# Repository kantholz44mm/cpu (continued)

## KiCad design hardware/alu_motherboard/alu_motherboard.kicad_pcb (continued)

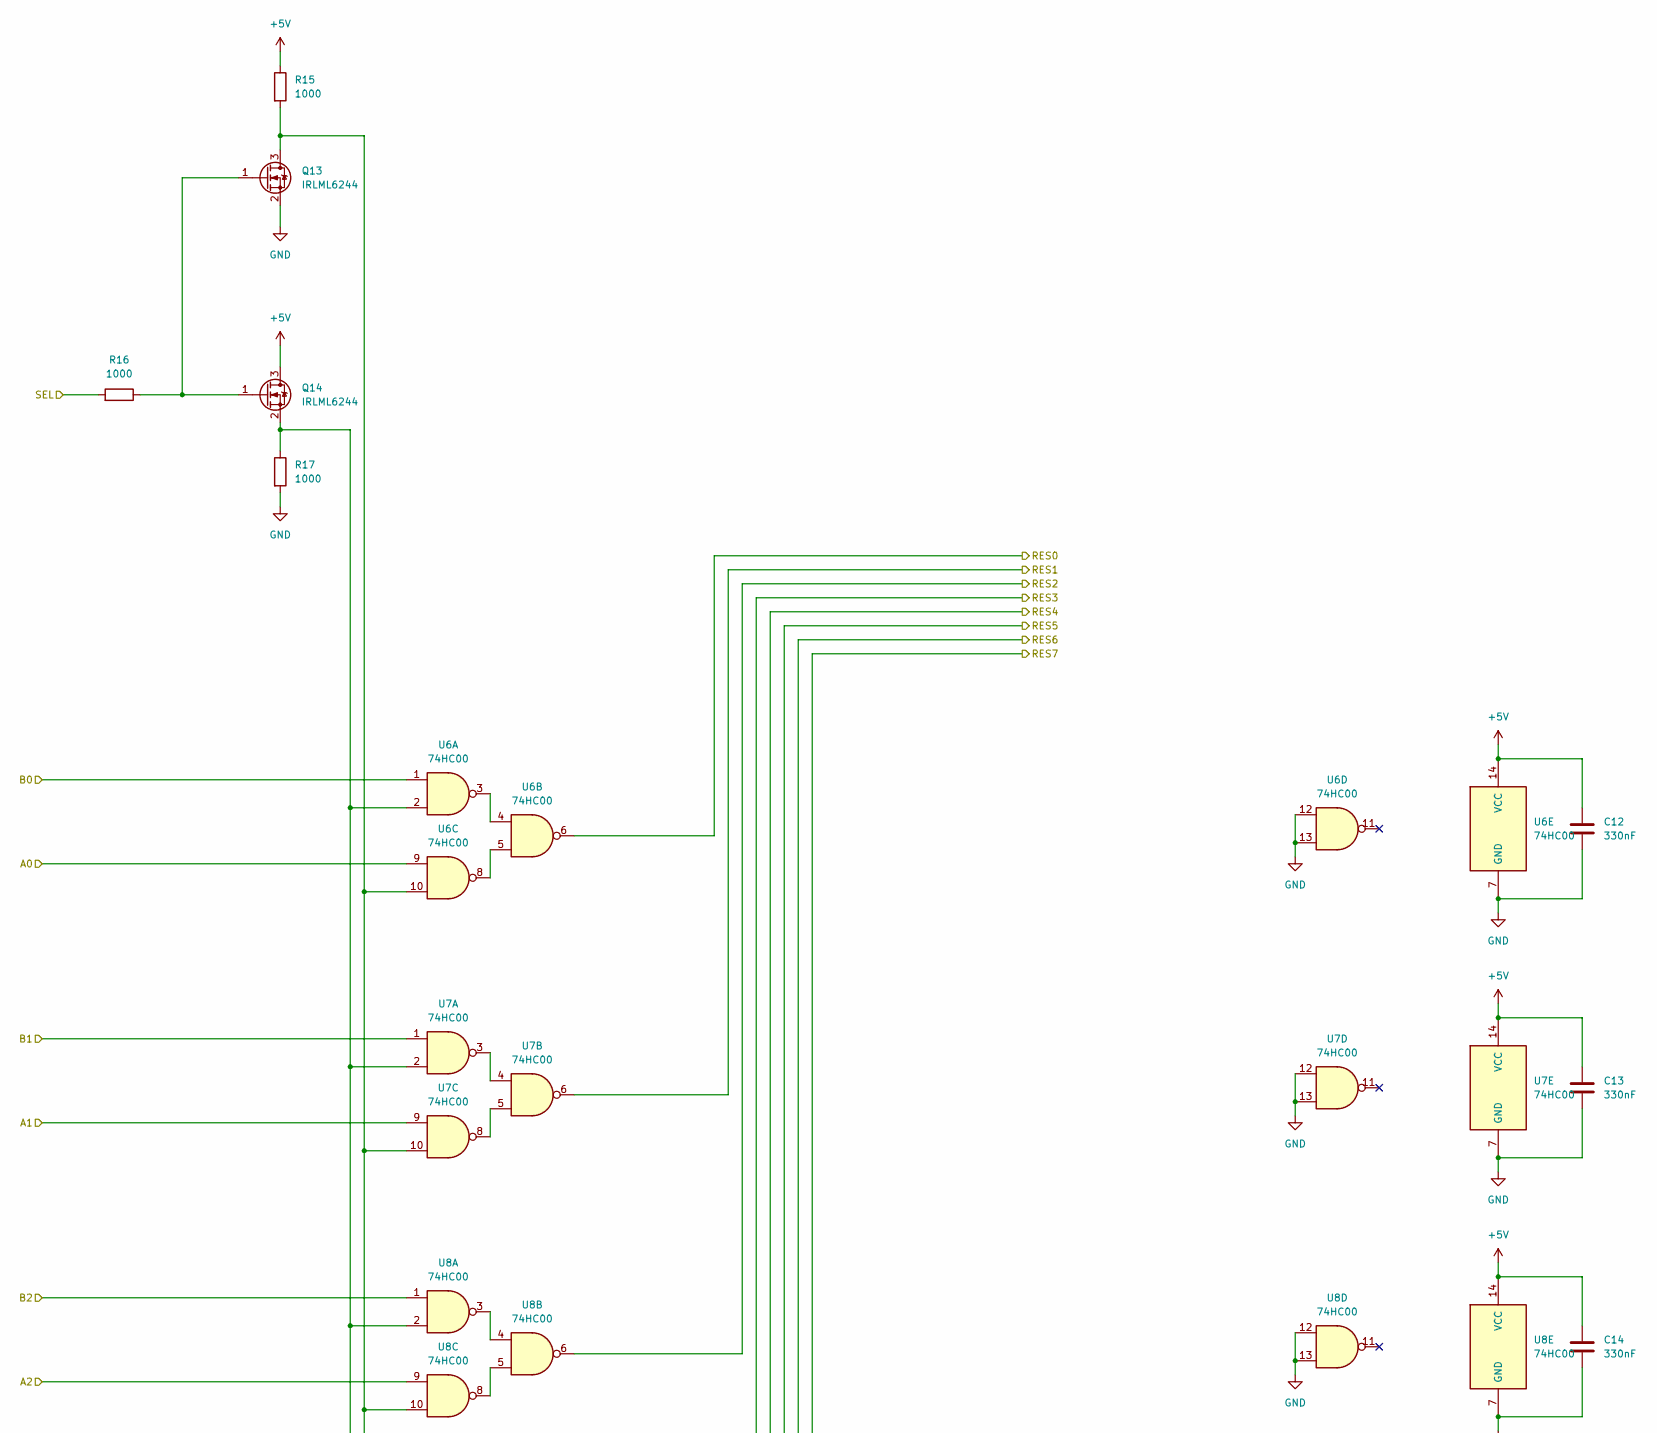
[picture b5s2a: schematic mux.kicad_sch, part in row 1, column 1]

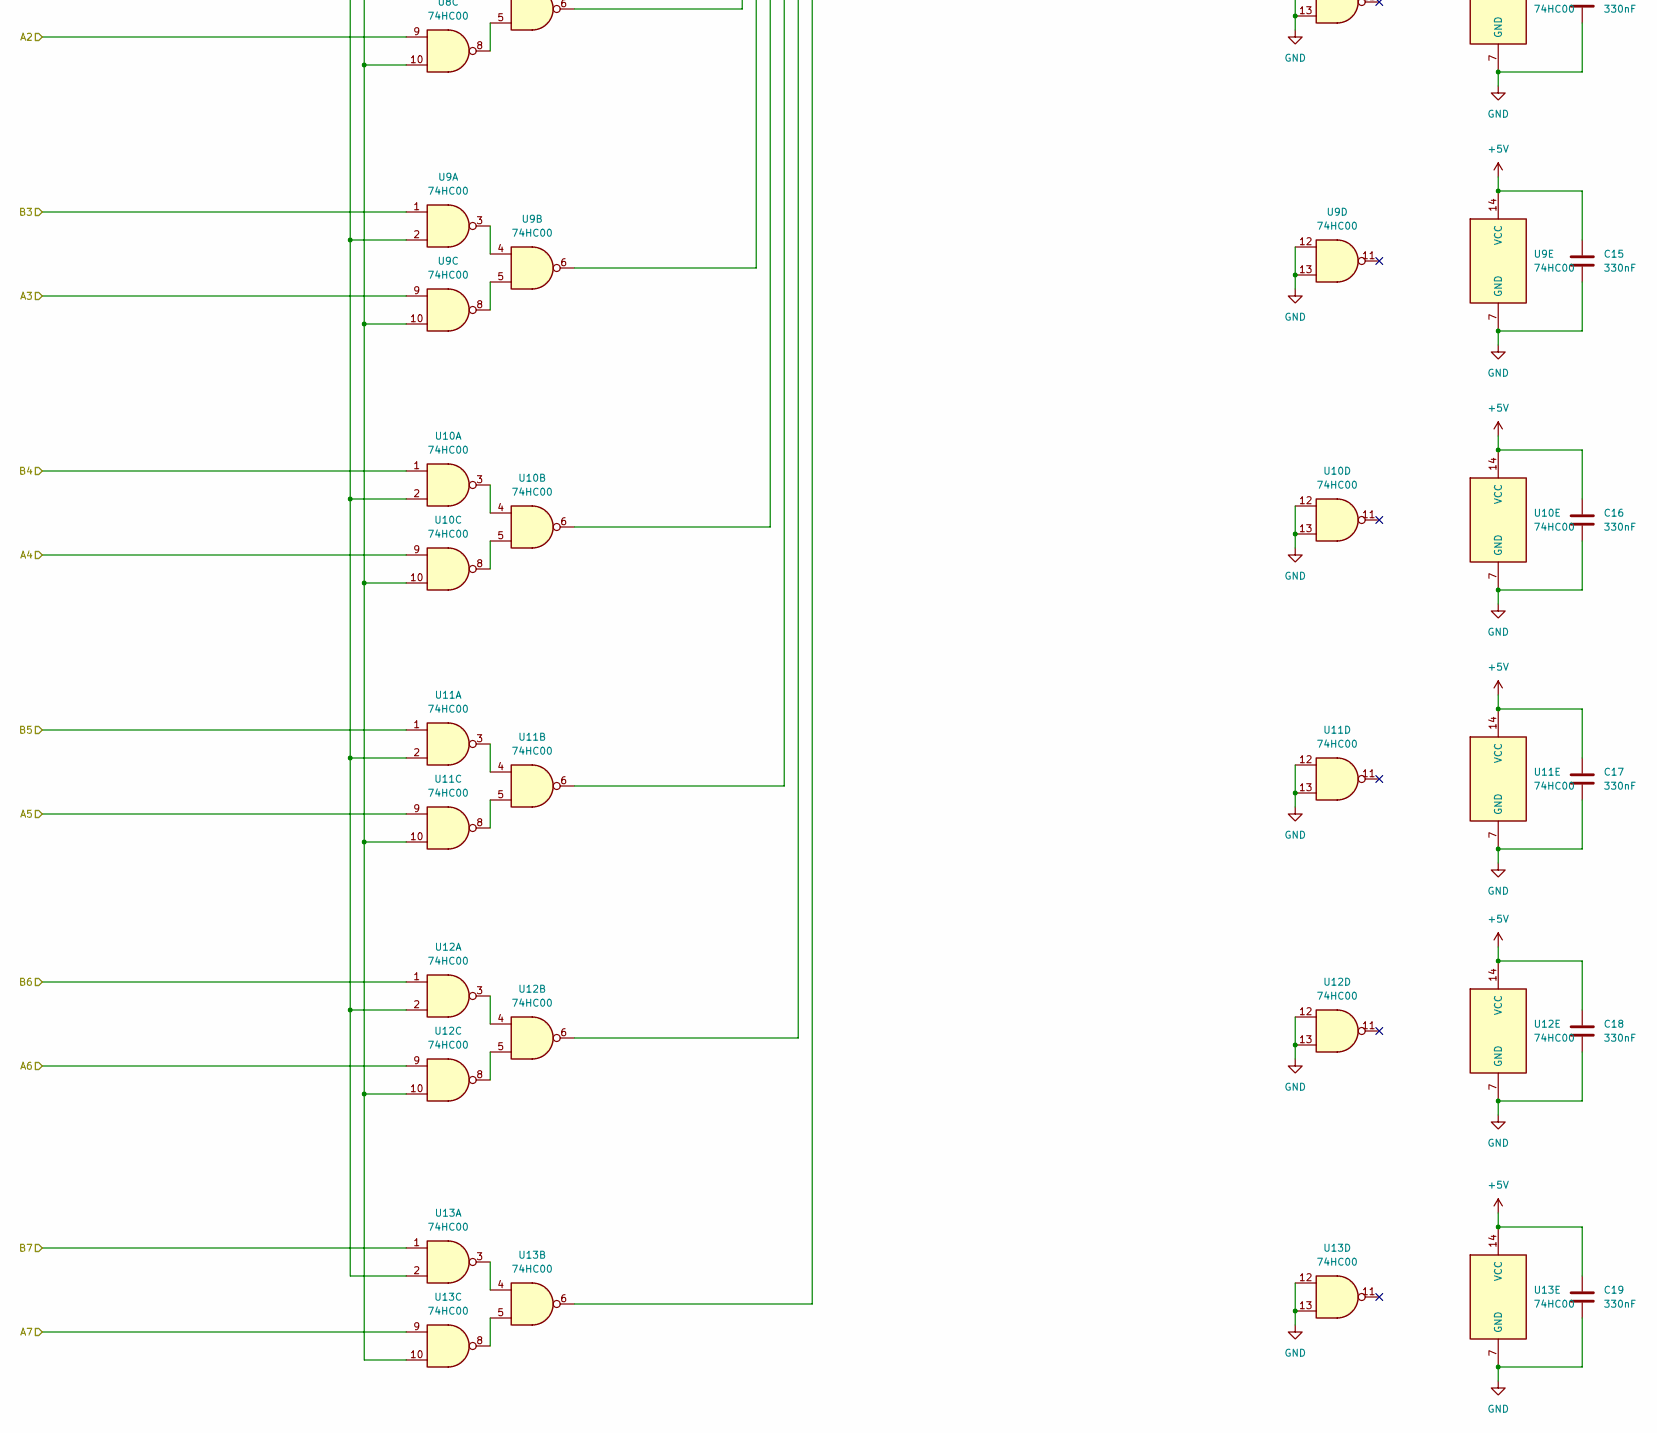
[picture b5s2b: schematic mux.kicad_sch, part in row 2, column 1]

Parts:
C12, C13, C14, C15, C16, C17, C18, C19: 330nF; C_0603_1608Metric_Pad1.08x0.95mm_HandSolder; LCSC C2918485
Q13, Q14: IRLML6244; SOT-23-3; LCSC C5123965
R15, R16, R17: 1000; R_0603_1608Metric_Pad0.98x0.95mm_HandSolder; LCSC C21190
U6, U7, U8, U9, U10, U11, U12, U13: 74HC00; SOIC-14_3.9x8.7mm_P1.27mm; LCSC C5586

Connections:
+5V: C12.1, C13.1, C14.1, C15.1, C16.1, C17.1, C18.1, C19.1, Q14.3 (D), R15.1, U6.14 (VCC), U7.14 (VCC), U8.14 (VCC), U9.14 (VCC), U10.14 (VCC), U11.14 (VCC), U12.14 (VCC), U13.14 (VCC); also elsewhere on the board
/ARES0: U6.9; also elsewhere on the board
/ARES1: U7.9; also elsewhere on the board
/ARES2: U8.9; also elsewhere on the board
/ARES3: U9.9; also elsewhere on the board
/ARES4: U10.9; also elsewhere on the board
/ARES5: U11.9; also elsewhere on the board
/ARES6: U12.9; also elsewhere on the board
/ARES7: U13.9; also elsewhere on the board
/BS1: R16.2; also elsewhere on the board
/MRES0: U6.6; also elsewhere on the board
/MRES1: U7.6; also elsewhere on the board
/MRES2: U8.6; also elsewhere on the board
/MRES3: U9.6; also elsewhere on the board
/MRES4: U10.6; also elsewhere on the board
/MRES5: U11.6; also elsewhere on the board
/MRES6: U12.6; also elsewhere on the board
/MRES7: U13.6; also elsewhere on the board
/SRES0: U6.1; also elsewhere on the board
/SRES1: U7.1; also elsewhere on the board
/SRES2: U8.1; also elsewhere on the board
/SRES3: U9.1; also elsewhere on the board
/SRES4: U10.1; also elsewhere on the board
/SRES5: U11.1; also elsewhere on the board
/SRES6: U12.1; also elsewhere on the board
/SRES7: U13.1; also elsewhere on the board
GND: C12.2, C13.2, C14.2, C15.2, C16.2, C17.2, C18.2, C19.2, Q13.2 (S), R17.2, U6.7 (GND), U6.12, U6.13, U7.7 (GND), U7.12, U7.13, U8.7 (GND), U8.12, U8.13, U9.7 (GND), U9.12, U9.13, U10.7 (GND), U10.12, U10.13, U11.7 (GND), U11.12, U11.13, U12.7 (GND), U12.12, U12.13, U13.7 (GND), U13.12, U13.13; also elsewhere on the board
unnamed: Q13.3 (D), R15.2, U6.10, U7.10, U8.10, U9.10, U10.10, U11.10, U12.10, U13.10
unnamed: Q13.1 (G), Q14.1 (G), R16.1
unnamed: Q14.2 (S), R17.1, U6.2, U7.2, U8.2, U9.2, U10.2, U11.2, U12.2, U13.2
unnamed: U6.3, U6.4
unnamed: U6.5, U6.8
unnamed: U7.3, U7.4
unnamed: U7.5, U7.8
unnamed: U8.3, U8.4
unnamed: U8.5, U8.8
unnamed: U9.3, U9.4
unnamed: U9.5, U9.8
unnamed: U10.3, U10.4
unnamed: U10.5, U10.8
unnamed: U11.3, U11.4
unnamed: U11.5, U11.8
unnamed: U12.3, U12.4
unnamed: U12.5, U12.8
unnamed: U13.3, U13.4
unnamed: U13.5, U13.8

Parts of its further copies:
C20, C21, C22, C23, C24, C25, C26, C27: 330nF; C_0603_1608Metric_Pad1.08x0.95mm_HandSolder; LCSC C2918485
Q15, Q16: IRLML6244; SOT-23-3; LCSC C5123965
R18, R19, R20: 1000; R_0603_1608Metric_Pad0.98x0.95mm_HandSolder; LCSC C21190
U14, U15, U16, U17, U18, U19, U20, U21: 74HC00; SOIC-14_3.9x8.7mm_P1.27mm; LCSC C5586

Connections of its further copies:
+5V: C20.1, C21.1, C22.1, C23.1, C24.1, C25.1, C26.1, C27.1, Q16.3 (D), R18.1, U14.14 (VCC), U15.14 (VCC), U16.14 (VCC), U17.14 (VCC), U18.14 (VCC), U19.14 (VCC), U20.14 (VCC), U21.14 (VCC); also elsewhere on the board
/8Bit_Mux3/RES0: U14.6; also elsewhere on the board
/8Bit_Mux3/RES1: U15.6; also elsewhere on the board
/8Bit_Mux3/RES2: U16.6; also elsewhere on the board
/8Bit_Mux3/RES3: U17.6; also elsewhere on the board
/8Bit_Mux3/RES4: U18.6; also elsewhere on the board
/8Bit_Mux3/RES5: U19.6; also elsewhere on the board
/8Bit_Mux3/RES6: U20.6; also elsewhere on the board
/8Bit_Mux3/RES7: U21.6; also elsewhere on the board
/BRES0: U14.1; also elsewhere on the board
/BRES1: U15.1; also elsewhere on the board
/BRES2: U16.1; also elsewhere on the board
/BRES3: U17.1; also elsewhere on the board
/BRES4: U18.1; also elsewhere on the board
/BRES5: U19.1; also elsewhere on the board
/BRES6: U20.1; also elsewhere on the board
/BRES7: U21.1; also elsewhere on the board
/MRES0: U14.9; also elsewhere on the board
/MRES1: U15.9; also elsewhere on the board
/MRES2: U16.9; also elsewhere on the board
/MRES3: U17.9; also elsewhere on the board
/MRES4: U18.9; also elsewhere on the board
/MRES5: U19.9; also elsewhere on the board
/MRES6: U20.9; also elsewhere on the board
/MRES7: U21.9; also elsewhere on the board
/OP2: R19.2; also elsewhere on the board
GND: C20.2, C21.2, C22.2, C23.2, C24.2, C25.2, C26.2, C27.2, Q15.2 (S), R20.2, U14.7 (GND), U14.12, U14.13, U15.7 (GND), U15.12, U15.13, U16.7 (GND), U16.12, U16.13, U17.7 (GND), U17.12, U17.13, U18.7 (GND), U18.12, U18.13, U19.7 (GND), U19.12, U19.13, U20.7 (GND), U20.12, U20.13, U21.7 (GND), U21.12, U21.13; also elsewhere on the board
unnamed: Q15.3 (D), R18.2, U14.10, U15.10, U16.10, U17.10, U18.10, U19.10, U20.10, U21.10
unnamed: Q15.1 (G), Q16.1 (G), R19.1
unnamed: Q16.2 (S), R20.1, U14.2, U15.2, U16.2, U17.2, U18.2, U19.2, U20.2, U21.2
unnamed: U14.3, U14.4
unnamed: U14.5, U14.8
unnamed: U15.3, U15.4
unnamed: U15.5, U15.8
unnamed: U16.3, U16.4
unnamed: U16.5, U16.8
unnamed: U17.3, U17.4
unnamed: U17.5, U17.8
unnamed: U18.3, U18.4
unnamed: U18.5, U18.8
unnamed: U19.3, U19.4
unnamed: U19.5, U19.8
unnamed: U20.3, U20.4
unnamed: U20.5, U20.8
unnamed: U21.3, U21.4
unnamed: U21.5, U21.8

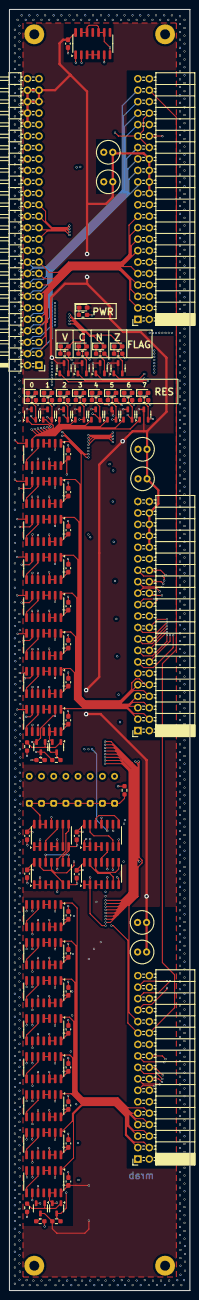
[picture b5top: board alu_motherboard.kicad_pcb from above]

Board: 4 copper layers, 40.0 x 284.0 mm, 113 parts (0 on the bottom side), 148 nets.

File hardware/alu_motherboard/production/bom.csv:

Designator,Footprint,Quantity,Value,LCSC Part #
"C10, C11, C12, C13, C14, C15, C16, C17, C18, C19, C20, C21, C22, C23, C24, C25, C26, C27, C7, C8, C9",0603,21,330nF,C2918485
"D1, D14, D15, D16, D17, D18, D19, D2, D20, D21, D3, D4, D5",0603,13,LED,C84267
"Q1, Q10, Q11, Q12, Q13, Q14, Q15, Q16, Q2, Q3, Q4, Q5, Q6, Q7, Q8, Q9",SOT-23-3,16,IRLML6244,C5123965
"R1, R10, R11, R12, R13, R14, R15, R16, R17, R18, R19, R2, R20, R3, R4, R5, R6, R7, R8, R9",0603,20,1000,C21190
"U1, U10, U11, U12, U13, U14, U15, U16, U17, U18, U19, U2, U20, U21, U3, U4, U5, U6, U7, U8, U9",SOIC-14_3.9x8.7mm_P1.27mm,21,74HC00,C5586

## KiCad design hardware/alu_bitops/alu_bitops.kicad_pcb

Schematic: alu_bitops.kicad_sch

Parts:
C1, C2, C3, C4, C5, C6, C7, C8, C9, C10, C11, C12, C13, C14, C15, C16, C17, C18, C19, C20, C21, C22, C23, C24, C25, C26, C27, C28, C29, C30, C31, C32, C33, C34, C35: 330nF; C_0603_1608Metric_Pad1.08x0.95mm_HandSolder; LCSC C2918485
C36, C37, C38: 10uF; C_0603_1608Metric_Pad1.08x0.95mm_HandSolder; LCSC C2909630
D1, D2, D3, D4, D5, D6, D7, D8, D9, D10, D11, D12, D13, D14, D15, D16, D17, D18, D19, D20, D21, D22, D23, D24, D25, D26, D27, D28, D29, D30, D63: LED; LED_0603_1608Metric_Pad1.05x0.95mm_HandSolder; LCSC C84267
D31, D32, D33, D34, D35, D36, D37, D38, D39, D40, D41, D42, D43, D44, D45, D46, D47, D48, D49, D50, D51, D52, D53, D54, D55, D56, D57, D58, D59, D60, D61, D62: D_Schottky; DO35_Packed; not fitted
H1, H2, H3, H4: MountingHole_Pad; MountingHole_2.2mm_M2_Pad
J1: Conn_02x21_Odd_Even; PinHeader_2x21_P2.54mm_Horizontal; not fitted
Q1, Q2, Q3, Q4, Q5, Q6, Q7, Q8, Q9, Q10, Q11, Q12, Q13, Q14, Q15, Q16, Q17, Q18, Q19, Q20, Q21, Q22, Q23, Q24, Q25, Q26, Q27, Q28, Q29, Q30: IRLML6244; SOT-23_Handsoldering; LCSC C5123965
R1, R2, R3, R4, R5, R6, R7, R8, R9, R10, R11, R12, R13, R14, R15, R16, R17, R18, R19, R20, R21, R22, R23, R24, R25, R26, R27, R28, R29, R30, R31, R32, R33, R34, R35, R36, R37, R38, R39: 1000; R_0603_1608Metric_Pad0.98x0.95mm_HandSolder; LCSC C21190
TP1, TP2, TP3, TP4, TP5, TP6, TP7, TP8, TP9, TP10, TP11, TP12, TP13, TP14, TP15, TP16, TP17, TP18, TP19, TP20: TestPoint; TestPoint_Pad_D2.0mm; not fitted
U1, U2, U3, U4, U5, U6, U7, U8, U9, U10, U11, U12, U13, U14, U15, U16, U17, U18, U19, U20, U21, U22, U23, U24, U25, U26, U27, U28, U29, U30, U31, U32, U33, U34, U35: 74HC00; SOIC-14_3.9x8.7mm_P1.27mm; LCSC C5586

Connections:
+5V: C1.1, C2.1, C3.1, C4.1, C5.1, C6.1, C7.1, C8.1, C9.1, C10.1, C11.1, C12.1, C13.1, C14.1, C15.1, C16.1, C17.1, C18.1, C19.1, C20.1, C21.1, C22.1, C23.1, C24.1, C25.1, C26.1, C27.1, C28.1, C29.1, C30.1, C31.1, C32.1, C33.1, C34.1, C35.1, C36.1, C37.1, C38.1, D63.2 (A), J1.34, J1.36, J1.38, J1.40, Q1.3 (D), Q2.3 (D), Q3.3 (D), Q4.3 (D), Q5.3 (D), Q6.3 (D), Q7.3 (D), Q8.3 (D), Q9.3 (D), Q10.3 (D), Q11.3 (D), Q12.3 (D), Q13.3 (D), Q14.3 (D), Q15.3 (D), Q16.3 (D), Q17.3 (D), Q18.3 (D), Q19.3 (D), Q20.3 (D), Q21.3 (D), Q22.3 (D), Q23.3 (D), Q24.3 (D), Q25.3 (D), Q26.3 (D), Q27.3 (D), Q28.3 (D), Q29.3 (D), Q30.3 (D), U1.14 (VCC), U2.14 (VCC), U3.14 (VCC), U4.14 (VCC), U5.14 (VCC), U6.14 (VCC), U7.14 (VCC), U8.14 (VCC), U9.14 (VCC), U10.14 (VCC), U11.14 (VCC), U12.14 (VCC), U13.14 (VCC), U14.14 (VCC), U15.14 (VCC), U16.14 (VCC), U17.14 (VCC), U18.14 (VCC), U19.14 (VCC), U20.14 (VCC), U21.14 (VCC), U22.14 (VCC), U23.14 (VCC), U24.14 (VCC), U25.14 (VCC), U26.14 (VCC), U27.14 (VCC), U28.14 (VCC), U29.14 (VCC), U30.14 (VCC), U31.14 (VCC), U32.14 (VCC), U33.14 (VCC), U34.14 (VCC), U35.14 (VCC)
/A0: J1.23, Q1.1 (G)
/A1: J1.24, Q2.1 (G)
/A2: J1.25, Q3.1 (G)
/A3: J1.26, Q4.1 (G)
/A4: J1.27, Q5.1 (G)
/A5: J1.28, Q6.1 (G)
/A6: J1.29, Q7.1 (G)
/A7: J1.30, Q8.1 (G)
/B0: J1.13, Q9.1 (G)
/B1: J1.14, Q10.1 (G)
/B2: J1.15, Q11.1 (G)
/B3: J1.16, Q12.1 (G)
/B4: J1.17, Q13.1 (G)
/B5: J1.18, Q14.1 (G)
/B6: J1.19, Q15.1 (G)
/B7: J1.20, Q16.1 (G)
/RES0: D19.2 (A), J1.3, Q19.2 (S)
/RES1: D20.2 (A), J1.4, Q20.2 (S)
/RES2: D21.2 (A), J1.5, Q21.2 (S)
/RES3: D22.2 (A), J1.6, Q22.2 (S)
/RES4: D23.2 (A), J1.7, Q23.2 (S)
/RES5: D24.2 (A), J1.8, Q24.2 (S)
/RES6: D25.2 (A), J1.9, Q25.2 (S)
/RES7: D26.2 (A), J1.10, Q26.2 (S)
/S0: J1.35, Q17.1 (G)
/S1: J1.37, Q18.1 (G)
GND: C1.2, C2.2, C3.2, C4.2, C5.2, C6.2, C7.2, C8.2, C9.2, C10.2, C11.2, C12.2, C13.2, C14.2, C15.2, C16.2, C17.2, C18.2, C19.2, C20.2, C21.2, C22.2, C23.2, C24.2, C25.2, C26.2, C27.2, C28.2, C29.2, C30.2, C31.2, C32.2, C33.2, C34.2, C35.2, C36.2, C37.2, C38.2, H1.1, H2.1, H3.1, H4.1, J1.1, J1.2, J1.11, J1.12, J1.21, J1.22, J1.31, J1.32, J1.33, J1.39, J1.41, J1.42, R1.2, R2.2, R3.2, R4.2, R5.2, R6.2, R7.2, R8.2, R9.2, R10.2, R11.2, R12.2, R13.2, R14.2, R15.2, R16.2, R17.2, R18.2, R19.2, R20.2, R21.2, R22.2, R23.2, R24.2, R25.2, R26.2, R27.2, R28.2, R29.2, R30.2, R31.2, R32.2, R33.2, R34.2, R35.2, R36.2, R37.2, R38.2, R39.2, U1.7 (GND), U2.7 (GND), U3.7 (GND), U4.7 (GND), U5.7 (GND), U6.7 (GND), U7.7 (GND), U8.7 (GND), U9.7 (GND), U10.7 (GND), U11.7 (GND), U12.7 (GND), U13.7 (GND), U14.7 (GND), U15.7 (GND), U16.7 (GND), U17.7 (GND), U18.7 (GND), U19.7 (GND), U20.7 (GND), U21.7 (GND), U22.7 (GND), U23.7 (GND), U24.7 (GND), U25.7 (GND), U26.7 (GND), U27.7 (GND), U28.7 (GND), U29.7 (GND), U30.7 (GND), U31.7 (GND), U32.7 (GND), U33.7 (GND), U33.9, U33.10, U33.12, U33.13, U34.7 (GND), U35.7 (GND)
unnamed: D1.2 (A), Q1.2 (S), U1.1, U1.2, U2.1, U2.4
unnamed: D1.1 (K), R1.1
unnamed: D2.2 (A), Q2.2 (S), U5.1, U5.2, U6.1, U6.4
unnamed: D2.1 (K), R2.1
unnamed: D3.2 (A), Q3.2 (S), U9.1, U9.2, U10.1, U10.4
unnamed: D3.1 (K), R3.1
unnamed: D4.2 (A), Q4.2 (S), U13.1, U13.2, U14.1, U14.4
unnamed: D4.1 (K), R4.1
unnamed: D5.2 (A), Q5.2 (S), U17.1, U17.2, U18.1, U18.4
unnamed: D5.1 (K), R5.1
unnamed: D6.2 (A), Q6.2 (S), U19.1, U19.2, U20.1, U20.4
unnamed: D6.1 (K), R6.1
unnamed: D7.2 (A), Q7.2 (S), U21.1, U21.2, U22.1, U22.4
unnamed: D7.1 (K), R7.1
unnamed: D8.2 (A), Q8.2 (S), U23.1, U23.2, U24.1, U24.4
unnamed: D8.1 (K), R8.1
unnamed: D9.2 (A), Q9.2 (S), U1.4, U1.5, U2.2, U2.10
unnamed: D9.1 (K), R9.1
unnamed: D10.2 (A), Q10.2 (S), U5.4, U5.5, U6.2, U6.10
unnamed: D10.1 (K), R10.1
unnamed: D11.2 (A), Q11.2 (S), U9.4, U9.5, U10.2, U10.10
unnamed: D11.1 (K), R11.1
unnamed: D12.2 (A), Q12.2 (S), U13.4, U13.5, U14.2, U14.10
unnamed: D12.1 (K), R12.1
unnamed: D13.2 (A), Q13.2 (S), U17.4, U17.5, U18.2, U18.10
unnamed: D13.1 (K), R13.1
unnamed: D14.2 (A), Q14.2 (S), U19.4, U19.5, U20.2, U20.10
unnamed: D14.1 (K), R14.1
unnamed: D15.2 (A), Q15.2 (S), U21.4, U21.5, U22.2, U22.10
unnamed: D15.1 (K), R15.1
unnamed: D16.2 (A), Q16.2 (S), U23.4, U23.5, U24.2, U24.10
unnamed: D16.1 (K), R16.1
unnamed: D17.2 (A), Q17.2 (S), TP17.1, U33.4, U33.5, U34.9, U35.9
unnamed: D17.1 (K), R17.1
unnamed: D18.2 (A), Q18.2 (S), TP19.1, U33.1, U33.2, U35.2, U35.10
unnamed: D18.1 (K), R18.1
unnamed: D19.1 (K), R19.1
unnamed: D20.1 (K), R20.1
unnamed: D21.1 (K), R21.1
unnamed: D22.1 (K), R22.1
unnamed: D23.1 (K), R23.1
unnamed: D24.1 (K), R24.1
unnamed: D25.1 (K), R25.1
unnamed: D26.1 (K), R26.1
unnamed: D27.2 (A), Q27.2 (S), U3.1, U7.1, U11.1, U15.1, U25.1, U27.1, U29.1, U31.1
unnamed: D27.1 (K), R27.1
unnamed: D28.2 (A), Q28.2 (S), U3.4, U7.4, U11.4, U15.4, U25.4, U27.4, U29.4, U31.4
unnamed: D28.1 (K), R28.1
unnamed: D29.2 (A), Q29.2 (S), U4.1, U8.1, U12.1, U16.1, U26.1, U28.1, U30.1, U32.1
unnamed: D29.1 (K), R29.1
unnamed: D30.2 (A), Q30.2 (S), U4.4, U8.4, U12.4, U16.4, U26.4, U28.4, U30.4, U32.4
unnamed: D30.1 (K), R30.1
unnamed: D31.2 (A), U3.8
unnamed: D31.1 (K), D32.1 (K), D33.1 (K), D34.1 (K), Q19.1 (G), R31.1
unnamed: D32.2 (A), U3.11
unnamed: D33.2 (A), U4.8
unnamed: D34.2 (A), U4.11
unnamed: D35.2 (A), U7.8
unnamed: D35.1 (K), D36.1 (K), D37.1 (K), D38.1 (K), Q20.1 (G), R32.1
unnamed: D36.2 (A), U7.11
unnamed: D37.2 (A), U8.8
unnamed: D38.2 (A), U8.11
unnamed: D39.2 (A), U11.8
unnamed: D39.1 (K), D40.1 (K), D41.1 (K), D42.1 (K), Q21.1 (G), R33.1
unnamed: D40.2 (A), U11.11
unnamed: D41.2 (A), U12.8
unnamed: D42.2 (A), U12.11
unnamed: D43.2 (A), U15.8
unnamed: D43.1 (K), D44.1 (K), D45.1 (K), D46.1 (K), Q22.1 (G), R34.1
unnamed: D44.2 (A), U15.11
unnamed: D45.2 (A), U16.8
unnamed: D46.2 (A), U16.11
unnamed: D47.2 (A), U25.8
unnamed: D47.1 (K), D48.1 (K), D49.1 (K), D50.1 (K), Q23.1 (G), R35.1
unnamed: D48.2 (A), U25.11
unnamed: D49.2 (A), U26.8
unnamed: D50.2 (A), U26.11
unnamed: D51.2 (A), U27.8
unnamed: D51.1 (K), D52.1 (K), D53.1 (K), D54.1 (K), Q24.1 (G), R36.1
unnamed: D52.2 (A), U27.11
unnamed: D53.2 (A), U28.8
unnamed: D54.2 (A), U28.11
unnamed: D55.2 (A), U29.8
unnamed: D55.1 (K), D56.1 (K), D57.1 (K), D58.1 (K), Q25.1 (G), R37.1
unnamed: D56.2 (A), U29.11
unnamed: D57.2 (A), U30.8
unnamed: D58.2 (A), U30.11
unnamed: D59.2 (A), U31.8
unnamed: D59.1 (K), D60.1 (K), D61.1 (K), D62.1 (K), Q26.1 (G), R38.1
unnamed: D60.2 (A), U31.11
unnamed: D61.2 (A), U32.8
unnamed: D62.2 (A), U32.11
unnamed: D63.1 (K), R39.1
unnamed: Q27.1 (G), U34.6
unnamed: Q28.1 (G), U34.11
unnamed: Q29.1 (G), U35.6
unnamed: Q30.1 (G), U35.11
unnamed: TP1.1, U1.8, U3.2
unnamed: TP2.1, U5.8, U7.2
unnamed: TP3.1, U9.8, U11.2
unnamed: TP4.1, U13.8, U15.2
unnamed: TP5.1, U17.8, U25.2
unnamed: TP6.1, U19.8, U27.2
unnamed: TP7.1, U21.8, U29.2
unnamed: TP8.1, U23.8, U31.2
unnamed: TP9.1, U1.12, U1.13, U2.3, U2.5, U2.9, U4.5
unnamed: TP10.1, U5.12, U5.13, U6.3, U6.5, U6.9, U8.5
unnamed: TP11.1, U9.12, U9.13, U10.3, U10.5, U10.9, U12.5
unnamed: TP12.1, U13.12, U13.13, U14.3, U14.5, U14.9, U16.5
unnamed: TP13.1, U17.12, U17.13, U18.3, U18.5, U18.9, U26.5
unnamed: TP14.1, U19.12, U19.13, U20.3, U20.5, U20.9, U28.5
unnamed: TP15.1, U21.12, U21.13, U22.3, U22.5, U22.9, U30.5
unnamed: TP16.1, U23.12, U23.13, U24.3, U24.5, U24.9, U32.5
unnamed: TP18.1, U33.6, U34.1, U35.1
unnamed: TP20.1, U33.3, U34.2, U34.10
unnamed: U1.3, U1.9
unnamed: U1.6, U1.10
unnamed: U1.11, U3.5
unnamed: U2.11, U4.2
unnamed: U2.6, U2.12
unnamed: U2.8, U2.13
unnamed: U3.3, U3.9, U3.10
unnamed: U3.6, U3.12, U3.13
unnamed: U4.3, U4.9, U4.10
unnamed: U4.6, U4.12, U4.13
unnamed: U5.3, U5.9
unnamed: U5.6, U5.10
unnamed: U5.11, U7.5
unnamed: U6.11, U8.2
unnamed: U6.6, U6.12
unnamed: U6.8, U6.13
unnamed: U7.3, U7.9, U7.10
unnamed: U7.6, U7.12, U7.13
unnamed: U8.3, U8.9, U8.10
unnamed: U8.6, U8.12, U8.13
unnamed: U9.3, U9.9
unnamed: U9.6, U9.10
unnamed: U10.11, U12.2
unnamed: U10.6, U10.12
unnamed: U10.8, U10.13
unnamed: U9.11, U11.5
unnamed: U11.3, U11.9, U11.10
unnamed: U11.6, U11.12, U11.13
unnamed: U12.3, U12.9, U12.10
unnamed: U12.6, U12.12, U12.13
unnamed: U13.3, U13.9
unnamed: U13.6, U13.10
unnamed: U13.11, U15.5
unnamed: U14.11, U16.2
unnamed: U14.6, U14.12
unnamed: U14.8, U14.13
unnamed: U15.3, U15.9, U15.10
unnamed: U15.6, U15.12, U15.13
unnamed: U16.3, U16.9, U16.10
unnamed: U16.6, U16.12, U16.13
unnamed: U17.3, U17.9
unnamed: U17.6, U17.10
unnamed: U17.11, U25.5
unnamed: U18.11, U26.2
unnamed: U18.6, U18.12
unnamed: U18.8, U18.13
unnamed: U19.3, U19.9
unnamed: U19.6, U19.10
unnamed: U19.11, U27.5
unnamed: U20.11, U28.2
unnamed: U20.6, U20.12
unnamed: U20.8, U20.13
unnamed: U21.3, U21.9
unnamed: U21.6, U21.10
unnamed: U21.11, U29.5
unnamed: U22.11, U30.2
unnamed: U22.6, U22.12
unnamed: U22.8, U22.13
unnamed: U23.3, U23.9
unnamed: U23.6, U23.10
unnamed: U23.11, U31.5
unnamed: U24.11, U32.2
unnamed: U24.6, U24.12
unnamed: U24.8, U24.13
unnamed: U25.3, U25.9, U25.10
unnamed: U25.6, U25.12, U25.13
unnamed: U26.3, U26.9, U26.10
unnamed: U26.6, U26.12, U26.13
unnamed: U27.3, U27.9, U27.10
unnamed: U27.6, U27.12, U27.13
unnamed: U28.3, U28.9, U28.10
unnamed: U28.6, U28.12, U28.13
unnamed: U29.3, U29.9, U29.10
unnamed: U29.6, U29.12, U29.13
unnamed: U30.3, U30.9, U30.10
unnamed: U30.6, U30.12, U30.13
unnamed: U31.3, U31.9, U31.10
unnamed: U31.6, U31.12, U31.13
unnamed: U32.3, U32.9, U32.10
unnamed: U32.6, U32.12, U32.13
unnamed: U34.3, U34.4, U34.5
unnamed: U34.8, U34.12, U34.13
unnamed: U35.3, U35.4, U35.5
unnamed: U35.8, U35.12, U35.13

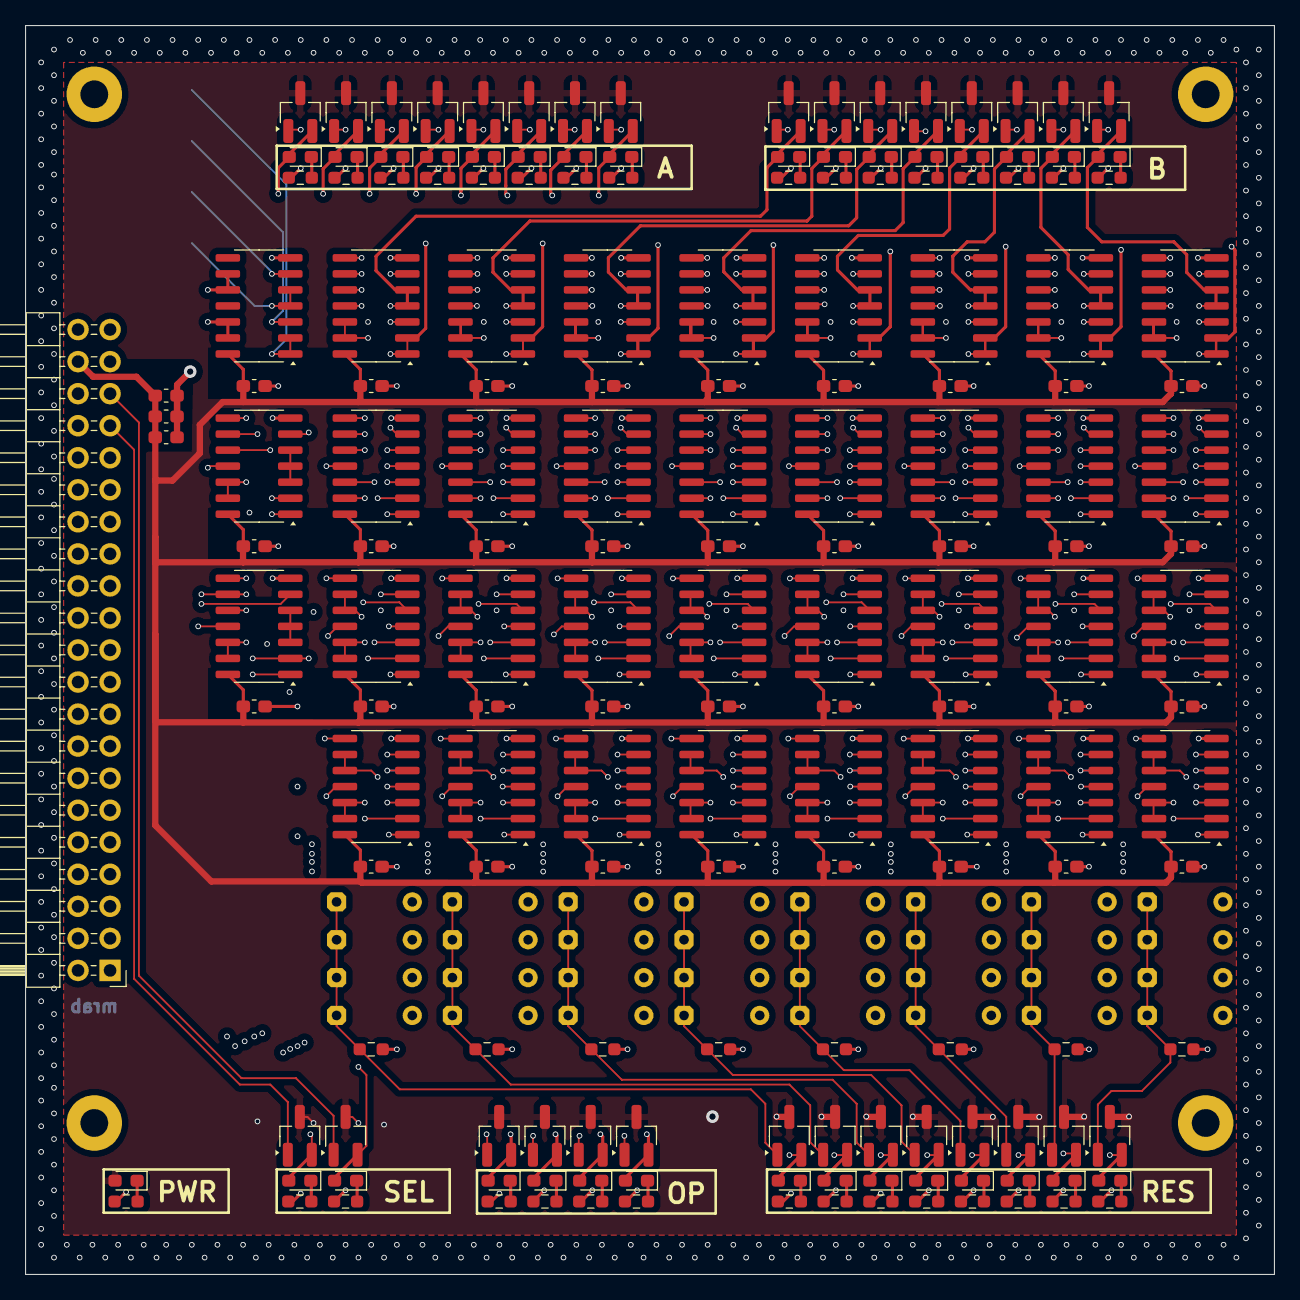
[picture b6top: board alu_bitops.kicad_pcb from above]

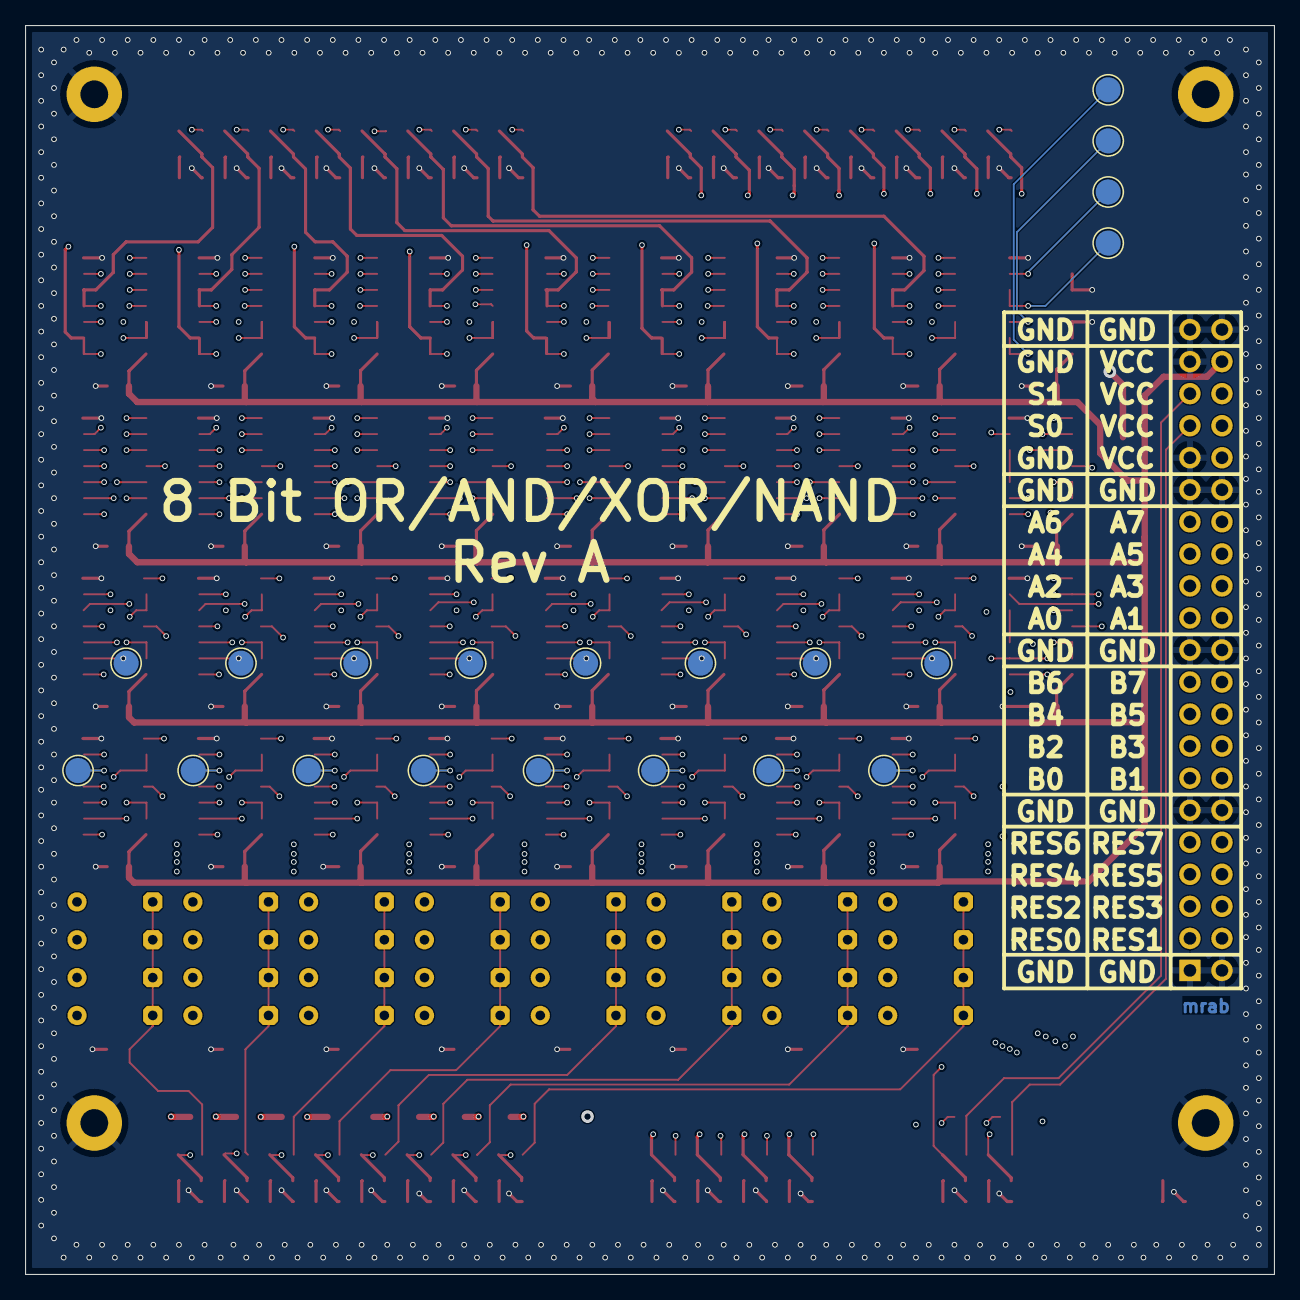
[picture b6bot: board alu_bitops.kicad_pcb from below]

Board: 4 copper layers, 99.0 x 99.0 mm, 230 parts (20 on the bottom side), 227 nets.

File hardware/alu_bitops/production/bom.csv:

Designator,Footprint,Quantity,Value,LCSC Part #
"C1, C10, C11, C12, C13, C14, C15, C16, C17, C18, C19, C2, C20, C21, C22, C23, C24, C25, C26, C27, C28, C29, C3, C30, C31, C32, C33, C34, C35, C4, C5, C6, C7, C8, C9",0603,35,330nF,C2918485
"C36, C37, C38",0603,3,10uF,C2909630
"D1, D10, D11, D12, D13, D14, D15, D16, D17, D18, D19, D2, D20, D21, D22, D23, D24, D25, D26, D27, D28, D29, D3, D30, D4, D5, D6, D63, D7, D8, D9",0603,31,LED,C84267
"Q1, Q10, Q11, Q12, Q13, Q14, Q15, Q16, Q17, Q18, Q19, Q2, Q20, Q21, Q22, Q23, Q24, Q25, Q26, Q27, Q28, Q29, Q3, Q30, Q4, Q5, Q6, Q7, Q8, Q9",SOT-23_Handsoldering,30,IRLML6244,C5123965
"R1, R10, R11, R12, R13, R14, R15, R16, R17, R18, R19, R2, R20, R21, R22, R23, R24, R25, R26, R27, R28, R29, R3, R30, R31, R32, R33, R34, R35, R36, R37, R38, R39, R4, R5, R6, R7, R8, R9",0603,39,1000,C21190
"U1, U10, U11, U12, U13, U14, U15, U16, U17, U18, U19, U2, U20, U21, U22, U23, U24, U25, U26, U27, U28, U29, U3, U30, U31, U32, U33, U34, U35, U4, U5, U6, U7, U8, U9",SOIC-14_3.9x8.7mm_P1.27mm,35,74HC00,C5586
